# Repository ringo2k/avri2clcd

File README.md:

avri2clcd
=========

LCD with I2C Interface for AVR Microntrollers based on peter fleury lib

PCB schematic can be found in [schematic](schematic) folder (eagle)

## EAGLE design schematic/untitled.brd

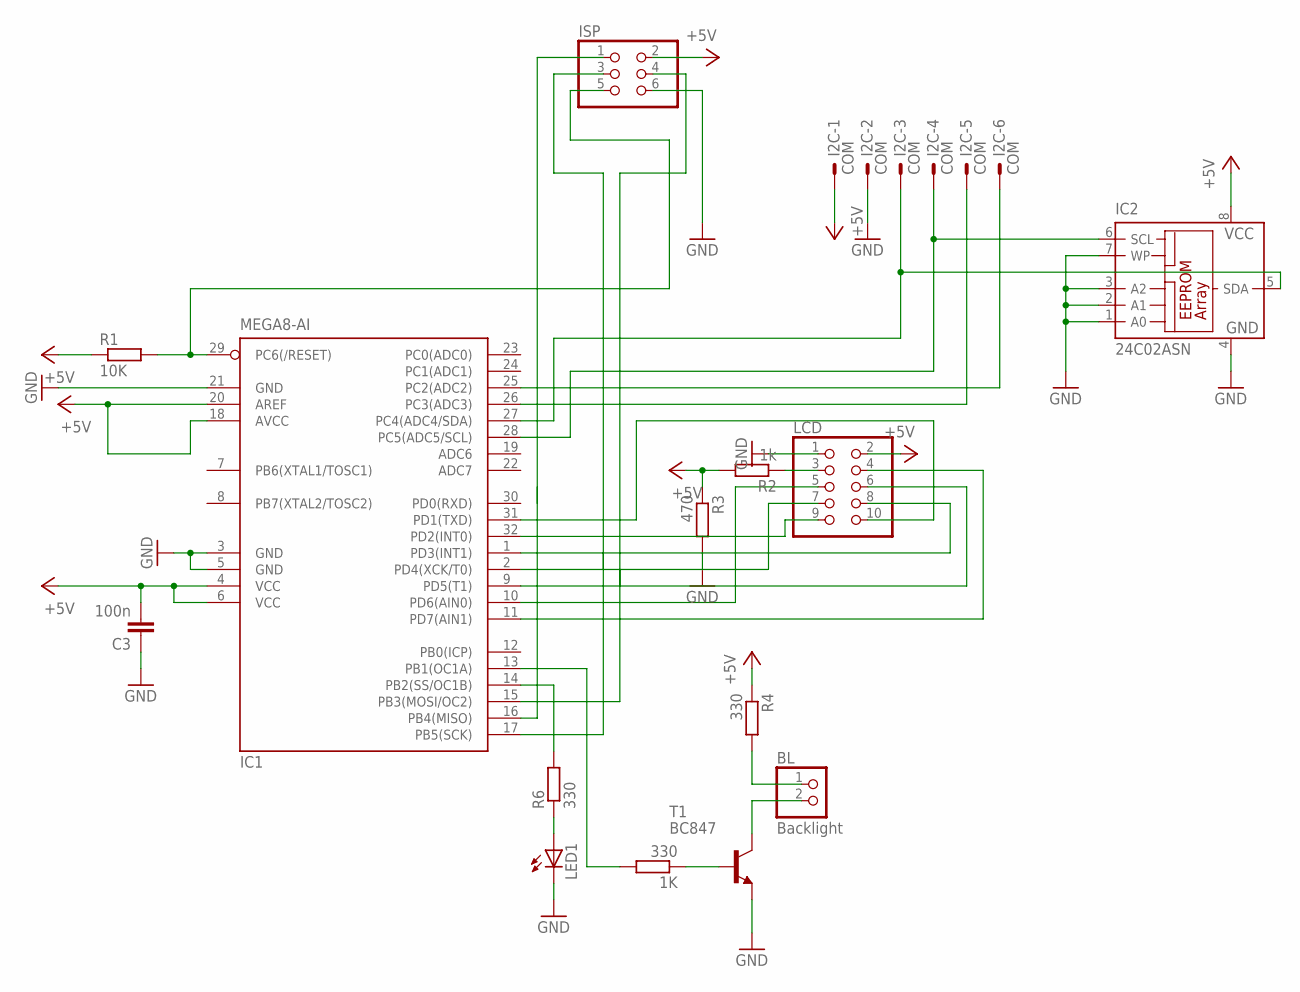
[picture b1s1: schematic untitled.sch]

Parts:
1K: 330; M0805
BL: Backlight; 1X02
C3: 100n; C0805
I2C: COM; ML6
IC1: MEGA8-AI; TQFP32-08
IC2: 24C02ASN; SO-08
ISP: PINHD-2X3; 2X03
LCD: PINHD-2X5; 2X05
LED1: LEDCHIP-LED0805; CHIP-LED0805
R1: 10K; M0805
R2: 1k; M0805
R3: 470; M0805
R4, R6: 330; M0805
T1: BC847; SOT23

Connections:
+5V: C3.2, I2C.1, IC1.4 (VCC), IC1.6 (VCC), IC1.18 (AVCC), IC1.20 (AREF), IC2.8 (VCC), ISP.2, LCD.2, R1.1, R2.2, R3.1, R4.1
GND: C3.1, I2C.2, IC1.3 (GND), IC1.5 (GND), IC1.21 (GND), IC2.1 (A0), IC2.2 (A1), IC2.3 (A2), IC2.4 (GND), IC2.7 (WP), ISP.6, LCD.1, LED1.C, R3.2, T1.2 (E)
unnamed: LCD.3, R2.1
unnamed: IC1.11 (PD7(AIN1)), LCD.4
unnamed: IC1.10 (PD6(AIN0)), LCD.5
unnamed: IC1.9 (PD5(T1)), LCD.6
unnamed: IC1.2 (PD4(XCK/T0)), LCD.7
unnamed: IC1.1 (PD3(INT1)), LCD.8
unnamed: IC1.32 (PD2(INT0)), LCD.9
unnamed: IC1.31 (PD1(TXD)), LCD.10
unnamed: BL.1, R4.2
unnamed: BL.2, T1.3 (C)
unnamed: 1K.1, T1.1 (B)
unnamed: 1K.2, IC1.13 (PB1(OC1A))
unnamed: I2C.3, IC1.27 (PC4(ADC4/SDA)), IC2.5 (SDA)
unnamed: IC1.14 (PB2(SS/OC1B)), R6.2
unnamed: I2C.4, IC1.28 (PC5(ADC5/SCL)), IC2.6 (SCL)
unnamed: I2C.5, IC1.26 (PC3(ADC3))
unnamed: IC1.15 (PB3(MOSI/OC2)), ISP.4
unnamed: IC1.16 (PB4(MISO)), ISP.1
unnamed: IC1.17 (PB5(SCK)), ISP.3
unnamed: I2C.6, IC1.25 (PC2(ADC2))
unnamed: IC1.29 (PC6(/RESET)), ISP.5, R1.2
unnamed: LED1.A, R6.1

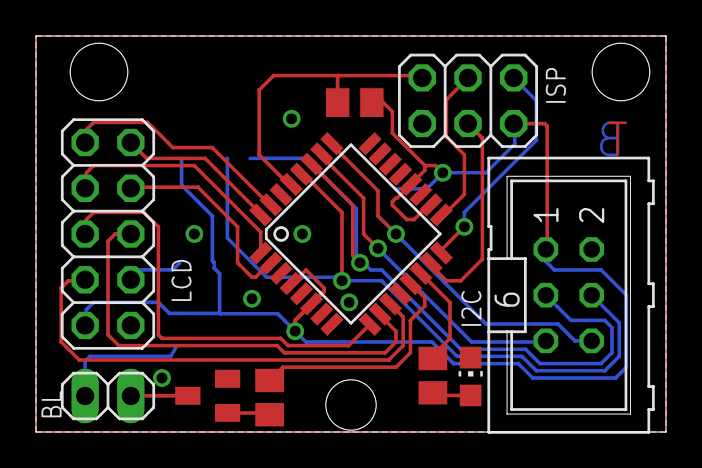
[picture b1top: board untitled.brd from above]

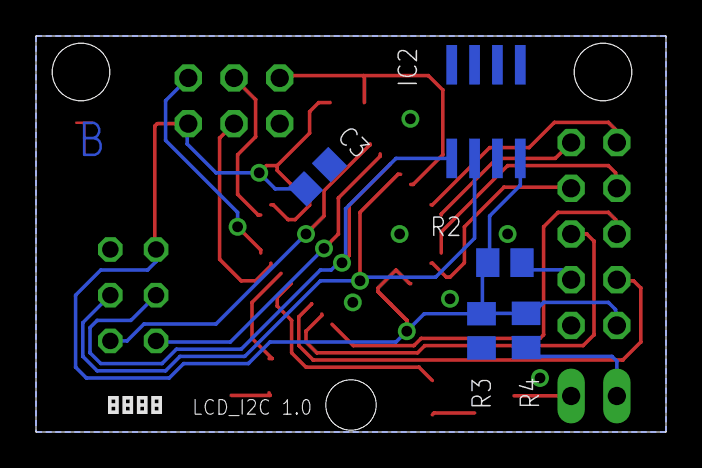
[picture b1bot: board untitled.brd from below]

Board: 2 copper layers, 35.0 x 22.0 mm, 16 parts (5 on the bottom side), 24 nets.

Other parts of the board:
U$1: LP_NUMBER_SILK_BOT

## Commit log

2014-03-04 main first checkin
2014-03-04 first blinking LED
2014-03-04 added schematics
2014-03-04 schematics
